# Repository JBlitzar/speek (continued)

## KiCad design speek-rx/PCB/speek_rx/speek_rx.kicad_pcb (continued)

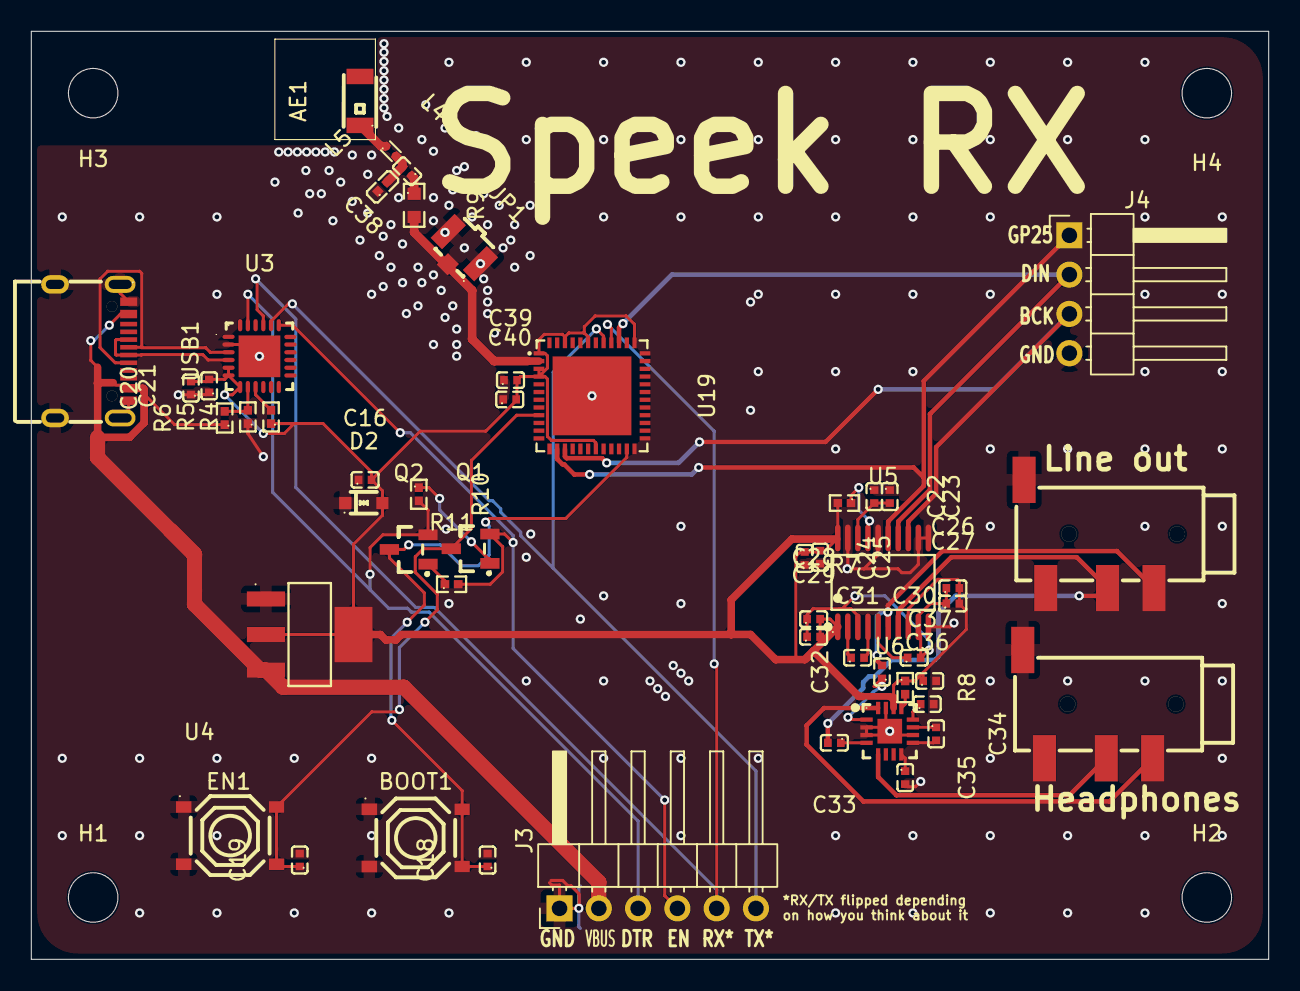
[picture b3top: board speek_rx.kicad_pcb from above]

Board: 2 copper layers, 80.0 x 60.0 mm, 55 parts (0 on the bottom side), 39 nets.

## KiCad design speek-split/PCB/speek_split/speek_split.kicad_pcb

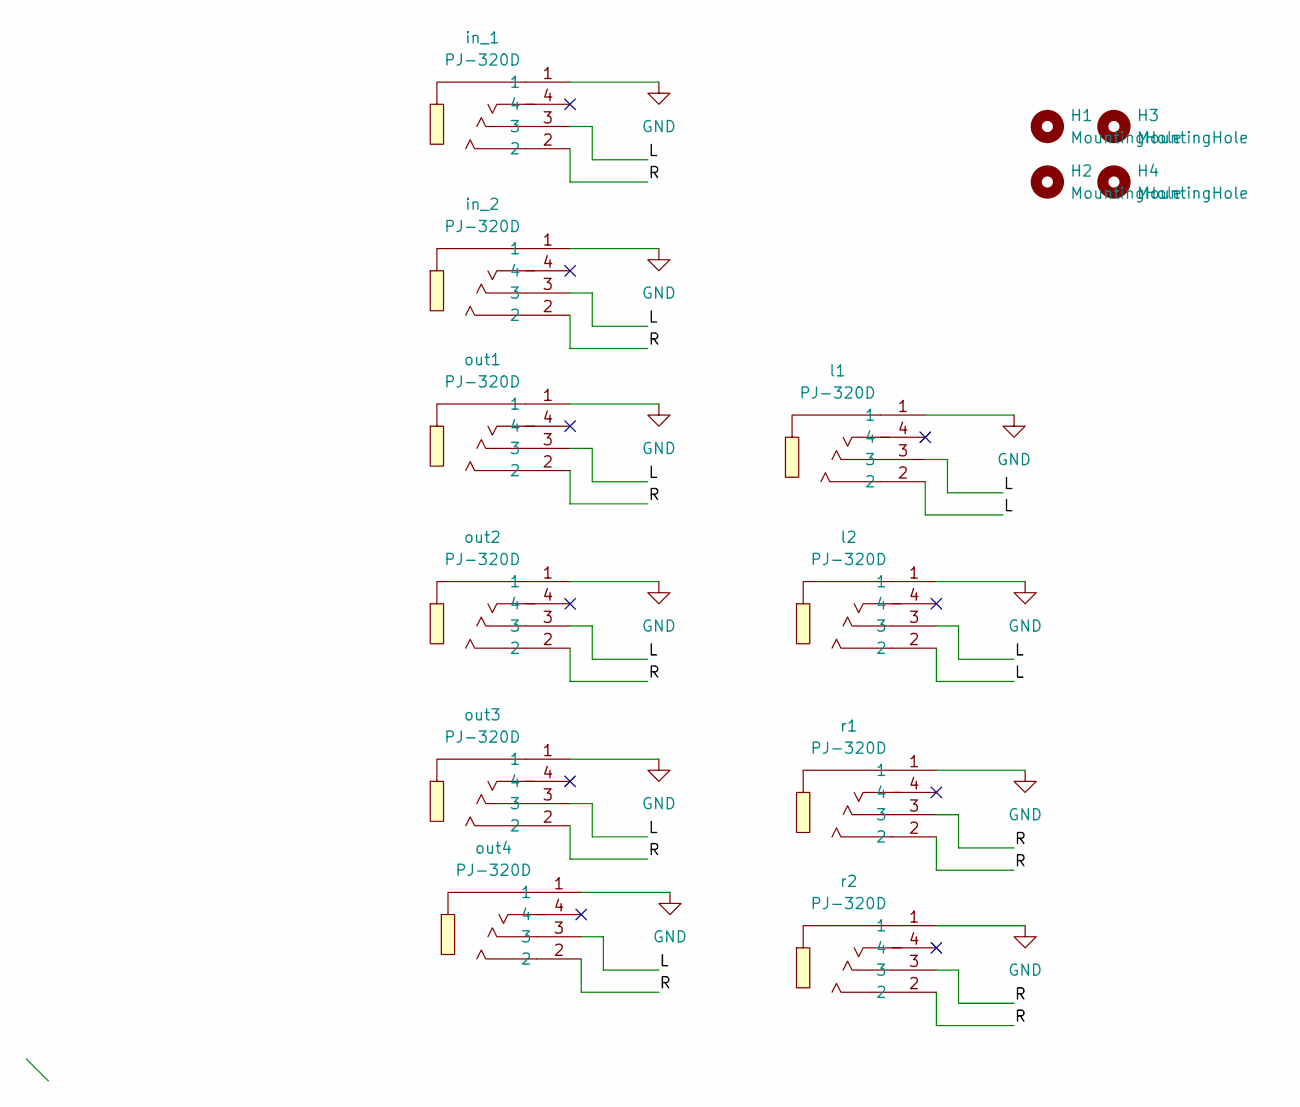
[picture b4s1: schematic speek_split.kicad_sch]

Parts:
H1, H2, H3, H4: MountingHole; MountingHole_3.2mm_M3
in_1, in_2: PJ-320D; AUDIO-SMD_PJ-320D-1; MPN PJ-320D; LCSC Part C431535
l1, l2: PJ-320D; AUDIO-SMD_PJ-320D-1; MPN PJ-320D; LCSC Part C431535
out1, out2, out3, out4: PJ-320D; AUDIO-SMD_PJ-320D-1; MPN PJ-320D; LCSC Part C431535
r1, r2: PJ-320D; AUDIO-SMD_PJ-320D-1; MPN PJ-320D; LCSC Part C431535

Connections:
/L: in_1.3, in_2.3, l1.2, l1.3, l2.2, l2.3, out1.3, out2.3, out3.3, out4.3
/R: in_1.2, in_2.2, out1.2, out2.2, out3.2, out4.2, r1.2, r1.3, r2.2, r2.3
GND: in_1.1, in_2.1, l1.1, l2.1, out1.1, out2.1, out3.1, out4.1, r1.1, r2.1

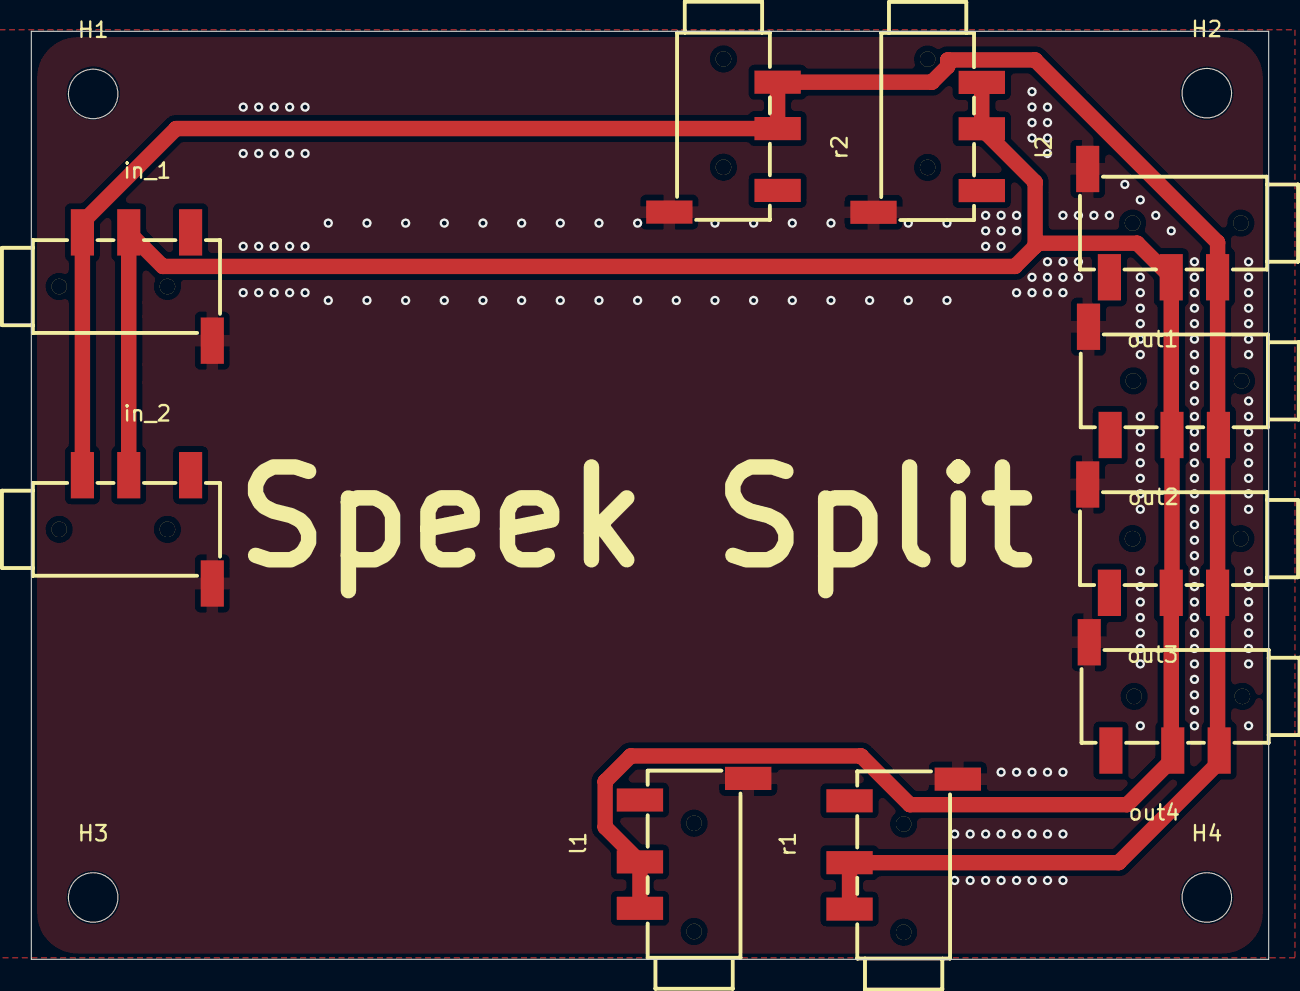
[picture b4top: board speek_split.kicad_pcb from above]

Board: 2 copper layers, 80.0 x 60.0 mm, 14 parts (0 on the bottom side), 3 nets.
